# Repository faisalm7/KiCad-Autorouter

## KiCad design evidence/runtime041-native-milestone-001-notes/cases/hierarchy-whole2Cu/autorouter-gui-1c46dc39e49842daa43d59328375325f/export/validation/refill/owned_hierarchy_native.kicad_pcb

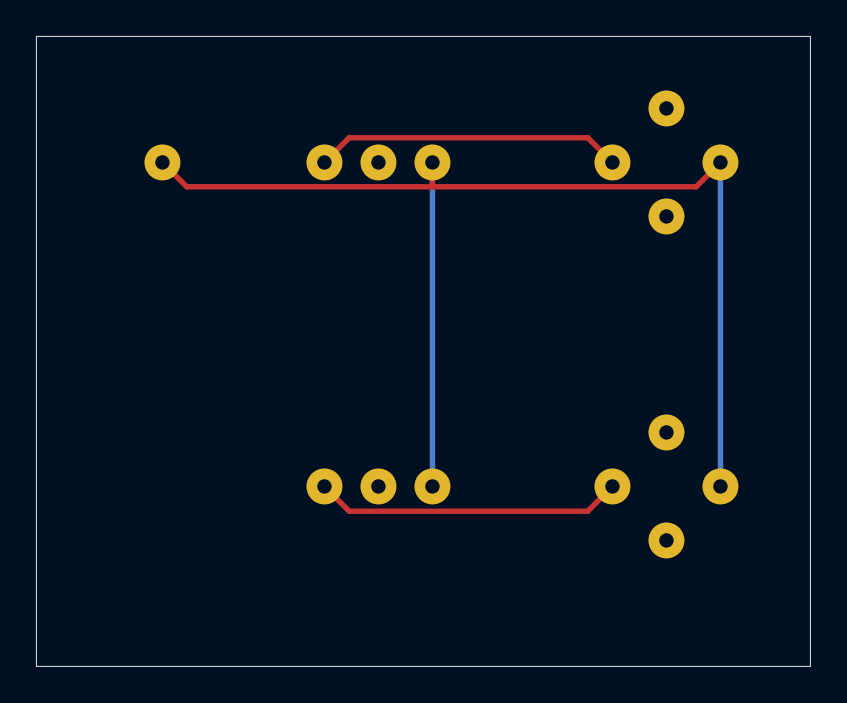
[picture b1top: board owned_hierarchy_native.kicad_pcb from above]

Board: 2 copper layers, 43.0 x 35.0 mm, 5 parts (0 on the bottom side), 3 nets.

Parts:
J1, J2: OWNED_ALIAS; owned_hierarchy_alias
U1, U2: OWNED_DUAL; owned_hierarchy_dual
X1: OWNED_TERMINAL; owned_hierarchy_terminal

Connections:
/A/SIG_A: J1.R, U1.1
/B/SIG_A: J2.R, U2.1
GND: J1.T, J2.T, U1.3, U2.3, X1.1

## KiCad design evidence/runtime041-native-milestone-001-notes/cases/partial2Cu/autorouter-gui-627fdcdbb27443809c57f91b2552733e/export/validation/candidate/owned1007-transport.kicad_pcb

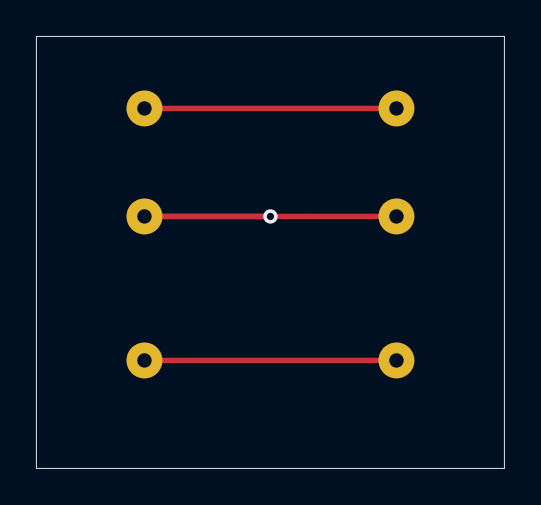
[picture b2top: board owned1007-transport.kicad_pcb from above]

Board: 2 copper layers, 26.0 x 24.0 mm, 8 parts (0 on the bottom side), 3 nets.

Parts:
J1, J2, J3, J4, J5, J6: owned1007_transport_terminal
MARK: OwnedMark; owned_task_copper_mark
MARK#2: OwnedMark; owned_task_copper_mark

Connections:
GND: J5.1, J6.1
KEEP: J3.1, J4.1
ROUTE: J1.1, J2.1

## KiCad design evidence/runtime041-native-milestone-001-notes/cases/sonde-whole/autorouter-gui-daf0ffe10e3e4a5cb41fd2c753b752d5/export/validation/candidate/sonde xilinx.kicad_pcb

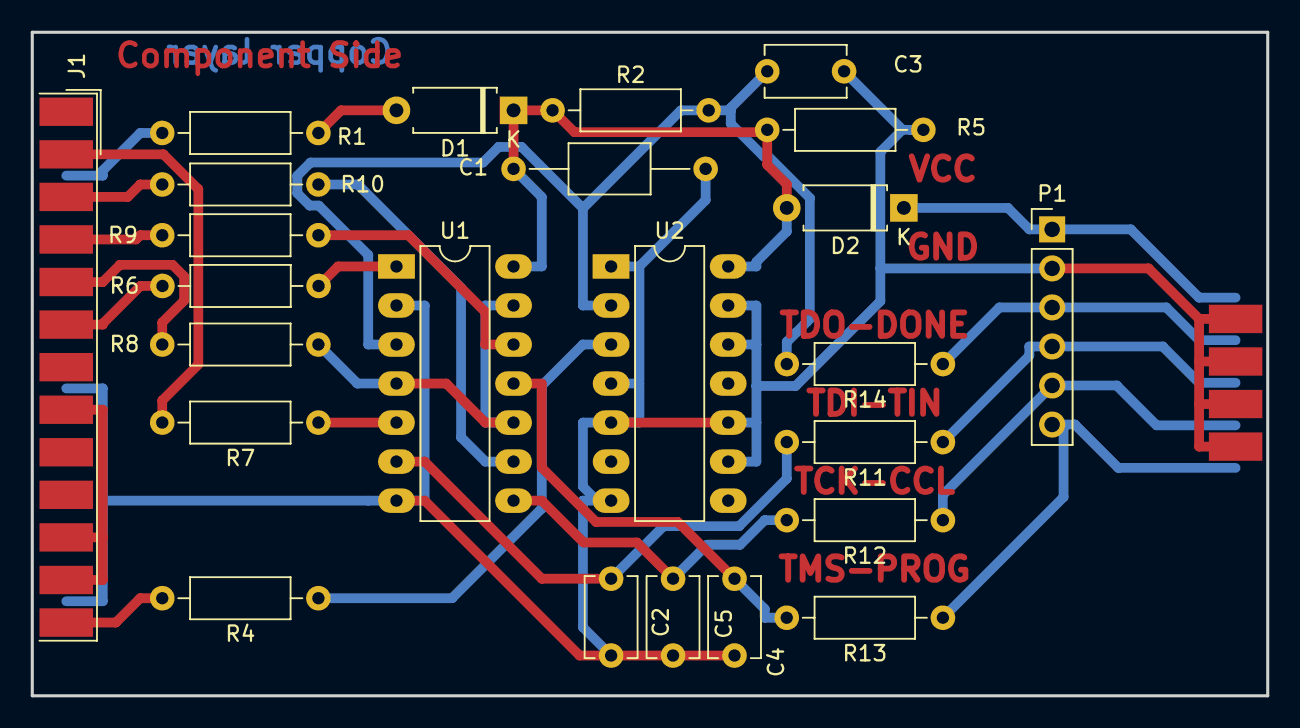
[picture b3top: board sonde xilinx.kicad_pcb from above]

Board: 2 copper layers, 80.4 x 43.2 mm, 25 parts (1 on the bottom side), 26 nets.

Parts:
C1: 1uF; C_Axial_L5.1mm_D3.1mm_P12.50mm_Horizontal
C2, C3, C4, C5: 100pF; C_Disc_D5.1mm_W3.2mm_P5.00mm
D1, D2: BAT46; D_A-405_P7.62mm_Horizontal
J1: DB25MALE; DSUB-25_Male_EdgeMount_P2.77mm
J2: DB9MALE; DSUB-9_Male_EdgeMount_P2.77mm
P1: CONN_6; PinHeader_1x06_P2.54mm_Vertical
R1, R6, R7, R8, R9, R10, R11, R12, R13, R14: 100; R_Axial_DIN0207_L6.3mm_D2.5mm_P10.16mm_Horizontal
R2: 5,1K; R_Axial_DIN0207_L6.3mm_D2.5mm_P10.16mm_Horizontal
R4: 47; R_Axial_DIN0207_L6.3mm_D2.5mm_P10.16mm_Horizontal
R5: 1K; R_Axial_DIN0207_L6.3mm_D2.5mm_P10.16mm_Horizontal
U1, U2: 74LS125; DIP-14_W7.62mm_LongPads

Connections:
/CLK-D1: J1.3, R10.2
/CTRL-D3: J1.5, R8.2
/DONE-SELECT*: J1.13, R4.2
/PWR_3,3-5V: D2.1 (A), J2.1, P1.1
/TCK-CCLK: J2.4, P1.5, R12.1
/TD0-DONE: J2.2, P1.3, R14.1
/TD0-PROG-D4: J1.6, R6.2
/TDI-DIN: J2.3, P1.4, R11.1
/TDI-DIN-D0: J1.2, R7.2
/TMS-PROG: J2.5, P1.6, R13.1
/TMS-PROG-D2: J1.4, R9.2
/VCC_SENSE-ERROR*: J1.15, R1.2
GND: C1.2, C2.2, C3.2, C4.2, C5.2, J1.20, J1.25, J2.6, J2.7, J2.8, J2.9, P1.2, R5.2, U1.2 (D), U1.7 (GND), U2.1 (E), U2.4 (E), U2.5 (D), U2.7 (GND), U2.9 (D), U2.10 (E), U2.12 (D), U2.13 (E)
unnamed: D1.2 (K), R1.1
unnamed: J1.8, J1.11, J1.12
unnamed: R6.1, U1.1 (E)
unnamed: C3.1, R2.2, R14.2, U1.3 (O), U2.2 (D)
unnamed: R7.1, U1.5 (D)
unnamed: R8.1, U1.4 (E), U1.10 (E), U1.13 (E)
unnamed: C2.1, R11.2, U1.6 (O)
unnamed: R10.1, U1.9 (D)
unnamed: C5.1, R12.2, U1.8 (O)
unnamed: R9.1, U1.12 (D)
unnamed: C4.1, R13.2, U1.11 (O)
unnamed: R4.1, U2.3 (O)
VCC: C1.1, D1.1 (A), D2.2 (K), R2.1, R5.1, U1.14 (VCC), U2.14 (VCC)
